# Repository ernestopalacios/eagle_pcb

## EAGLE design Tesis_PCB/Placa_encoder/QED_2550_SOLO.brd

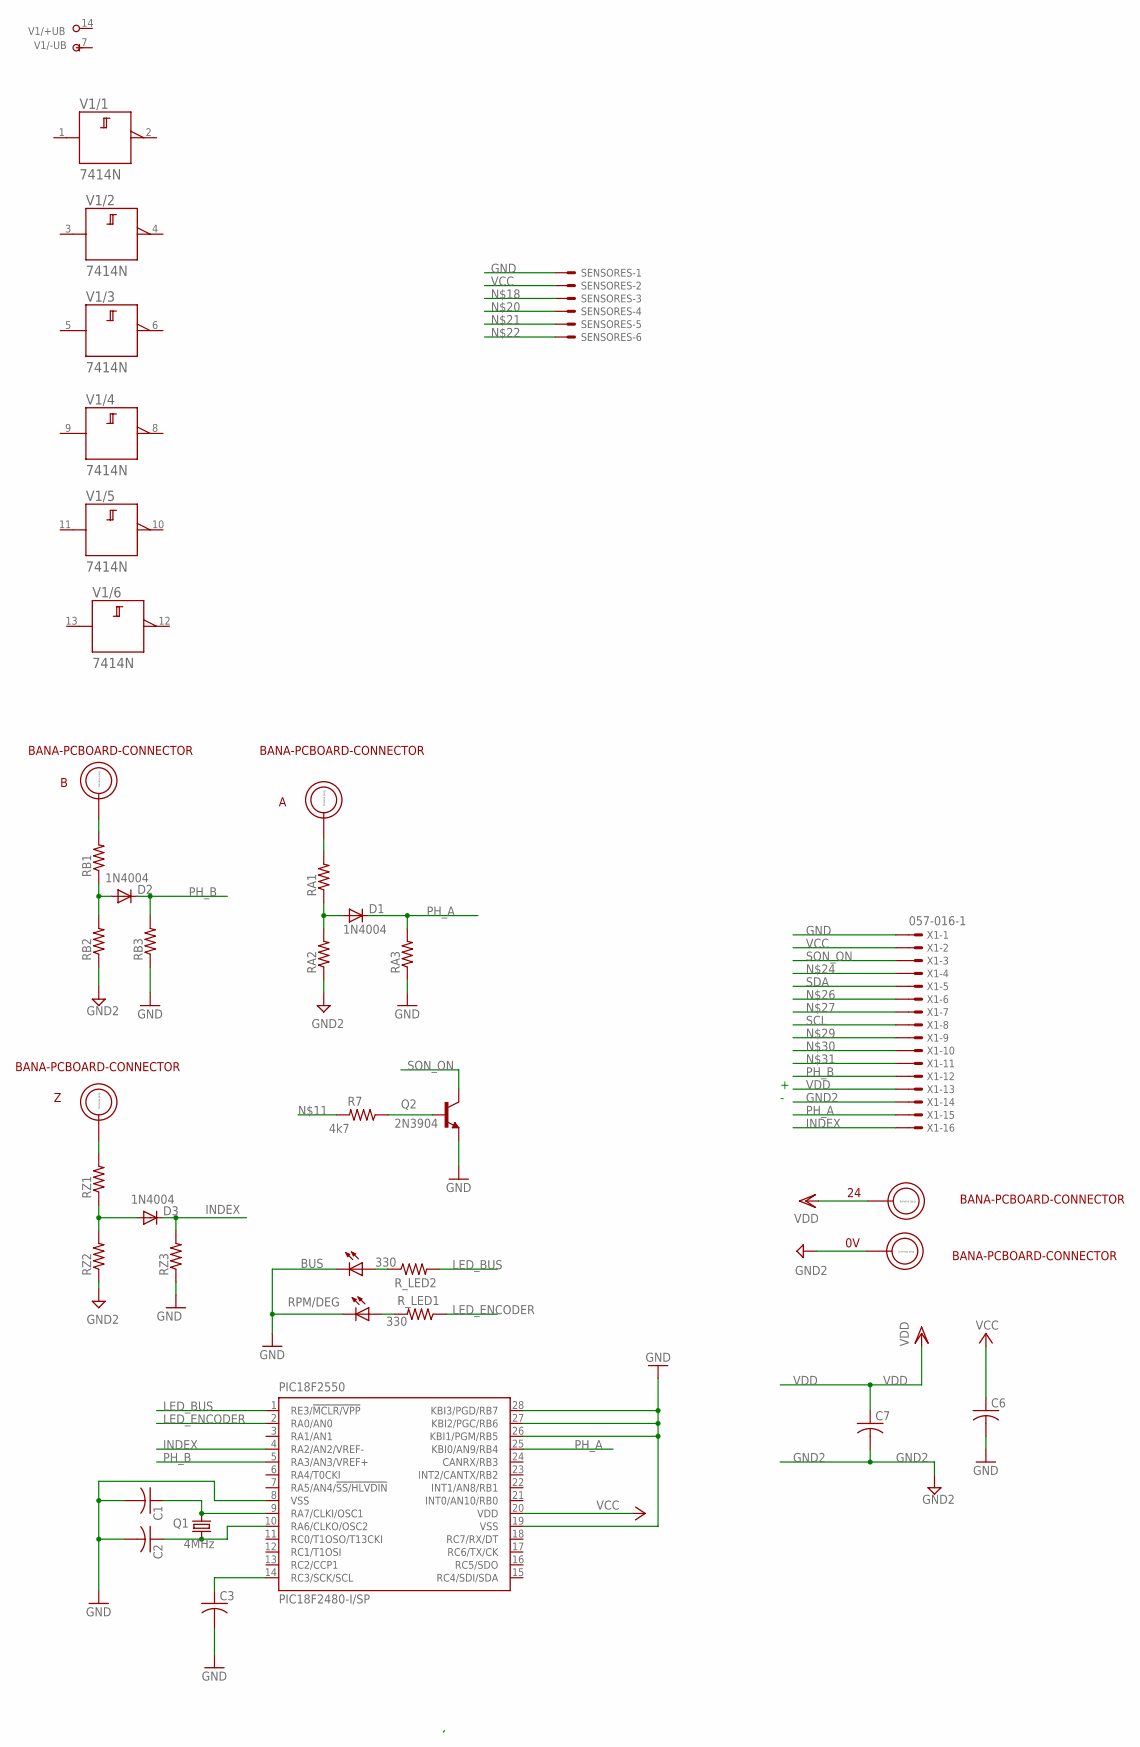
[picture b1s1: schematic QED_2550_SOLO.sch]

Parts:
0V, 24: BANA-PCBOARD-CONNECTOR; BANA_PLUG
A: BANA-PCBOARD-CONNECTOR; BANA_PLUG
B: BANA-PCBOARD-CONNECTOR; BANA_PLUG
BUS: LED5MM
C1, C2, C3: C-US025-024X044; C025-024X044
C6, C7: C-US025-030X050; C025-030X050
D1, D2, D3: 1N4004; DO41-10
PIC18F2550: PIC18F2480-I/SP; DIL28-3
Q1: 4MHz; HC49/S
Q2: 2N3904; TO92
R7: 4k7; 0204/7
RA1, RA2, RA3: R-US_0204/7; 0204/7
RB1, RB2, RB3: R-US_0204/7; 0204/7
RPM/DEG: LED5MM
RZ1, RZ2, RZ3: R-US_0204/7; 0204/7
R_LED1, R_LED2: 330; 0204/7
SENSORES: 22-23-2061
V1: 7414N; DIL14
X1: 057-016-1
Z: BANA-PCBOARD-CONNECTOR; BANA_PLUG

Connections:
+UB: V1.14 (+UB)
-UB: V1.7 (-UB)
GND: BUS.K (C), C1.2, C2.2, C3.2, C6.2, PIC18F2550.8 (VSS), PIC18F2550.19 (VSS), PIC18F2550.26 (KBI1/PGM/RB5), PIC18F2550.27 (KBI2/PGC/RB6), PIC18F2550.28 (KBI3/PGD/RB7), Q2.3 (E), RA3.1, RB3.1, RPM/DEG.K (C), RZ3.1, SENSORES.1, X1.1
GND2: 0V.P$1, C7.2, RA2.1, RB2.1, RZ2.1, X1.14
INDEX: D3.C, PIC18F2550.4 (RA2/AN2/VREF-), RZ3.2, X1.16
LED_BUS: PIC18F2550.1 (RE3/!MCLR/VPP), R_LED2.2
LED_ENCODER: PIC18F2550.2 (RA0/AN0), R_LED1.1
unnamed: C1.1, PIC18F2550.9 (RA7/CLKI/OSC1), Q1.2
unnamed: C2.1, PIC18F2550.10 (RA6/CLKO/OSC2), Q1.1
unnamed: C3.1, PIC18F2550.14 (RC3/SCK/SCL)
unnamed: BUS.A, R_LED2.1
unnamed: RPM/DEG.A, R_LED1.2
unnamed: D1.A, RA1.1, RA2.2
unnamed: Q2.2 (B), R7.1
unnamed: D2.A, RB1.1, RB2.2
unnamed: RZ1.2, Z.P$1
unnamed: B.P$1, RB1.2
unnamed: A.P$1, RA1.2
unnamed: D3.A, RZ1.1, RZ2.2
PH_A: D1.C, PIC18F2550.25 (KBI0/AN9/RB4), RA3.2, X1.15
PH_B: D2.C, PIC18F2550.5 (RA3/AN3/VREF+), RB3.2, X1.12
SCL: X1.8
SDA: X1.5
SON_ON: Q2.1 (C), X1.3
VCC: C6.1, PIC18F2550.20 (VDD), SENSORES.2, X1.2
VDD: 24.P$1, C7.1, X1.13

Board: 2 copper layers, 33 parts (0 on the bottom side), 22 nets, no tracks yet.

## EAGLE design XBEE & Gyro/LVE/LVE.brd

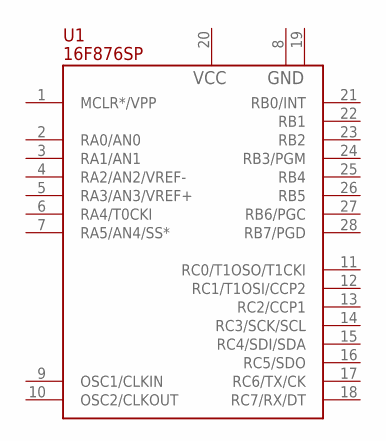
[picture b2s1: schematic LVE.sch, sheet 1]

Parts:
U1: 16F876SP; DIL28-3

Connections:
VCC: U1.20 (VCC); also elsewhere on the board

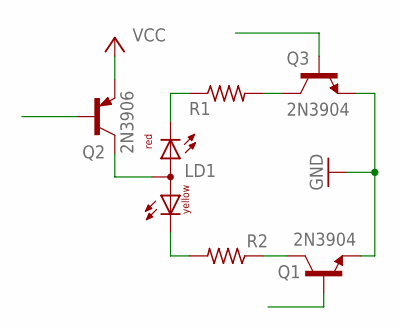
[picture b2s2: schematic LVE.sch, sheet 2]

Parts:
LD1: DUOLED-RY-A; DUOLED-A-5MM
Q1, Q3: 2N3904; TO92
Q2: 2N3906; TO92
R1, R2: R-US_0204/5; 0204/5

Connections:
GND: Q1.3 (E), Q3.3 (E)
unnamed: LD1.A, Q2.1 (C)
unnamed: LD1.CR, R1.1
unnamed: LD1.CX (CY), R2.2
unnamed: Q1.1 (C), R2.1
unnamed: Q3.1 (C), R1.2
VCC: Q2.3 (E); also elsewhere on the board

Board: 2 copper layers, 7 parts (0 on the bottom side), 7 nets, no tracks yet.

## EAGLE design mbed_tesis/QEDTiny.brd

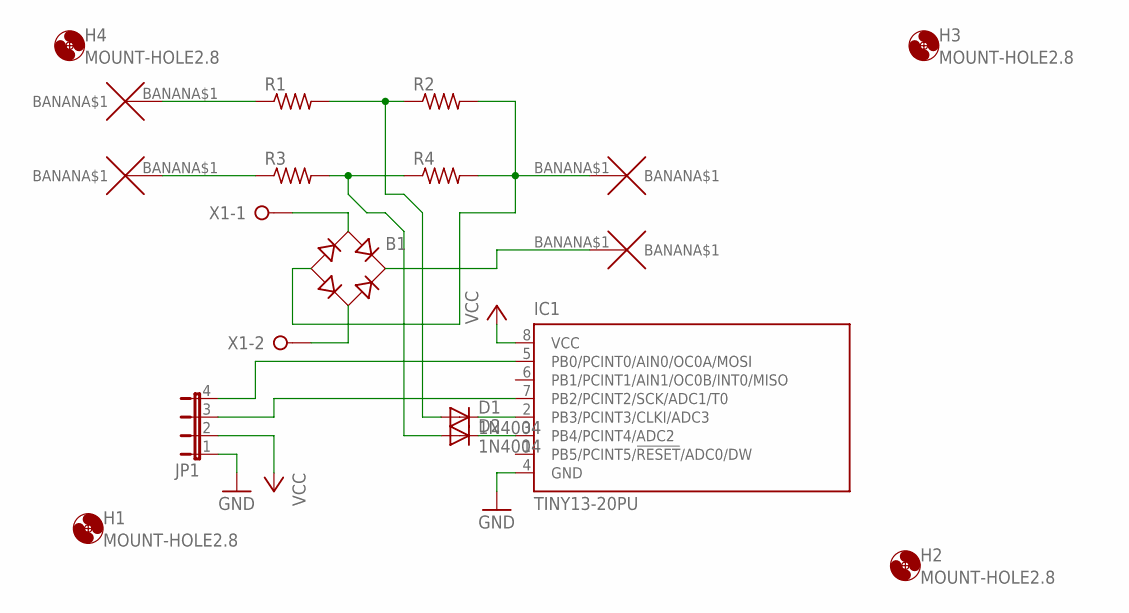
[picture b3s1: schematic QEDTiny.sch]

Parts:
B1: RB1A
D1, D2: 1N4004; DO41-10
H1, H2, H3, H4: MOUNT-HOLE2.8; 2,8
IC1: TINY13-20PU; DIL08
JP1: JP4E; JP4
R1, R2, R3, R4: R-US_0207/7; 0207/7
U$1, U$2, U$3, U$4: BANANA
X1: W237-02P; W237-132

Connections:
GND: IC1.4 (GND), JP1.1
unnamed: IC1.7 (PB2/PCINT2/SCK/ADC1/T0), JP1.3
unnamed: IC1.5 (PB0/PCINT0/AIN0/OC0A/MOSI), JP1.4
unnamed: R1.1, U$3.BANANA$1
unnamed: R3.1, U$4.BANANA$1
unnamed: D1.A, R1.2, R2.1
unnamed: D2.A, R3.2, R4.1
unnamed: B1.-, R2.2, R4.2, U$2.BANANA$1
unnamed: B1.AC1, X1.1
unnamed: B1.AC2, X1.2
unnamed: B1.+, U$1.BANANA$1
unnamed: D1.C, IC1.2 (PB3/PCINT3/CLKI/ADC3)
unnamed: D2.C, IC1.3 (PB4/PCINT4/ADC2)
VCC: IC1.8 (VCC), JP1.2

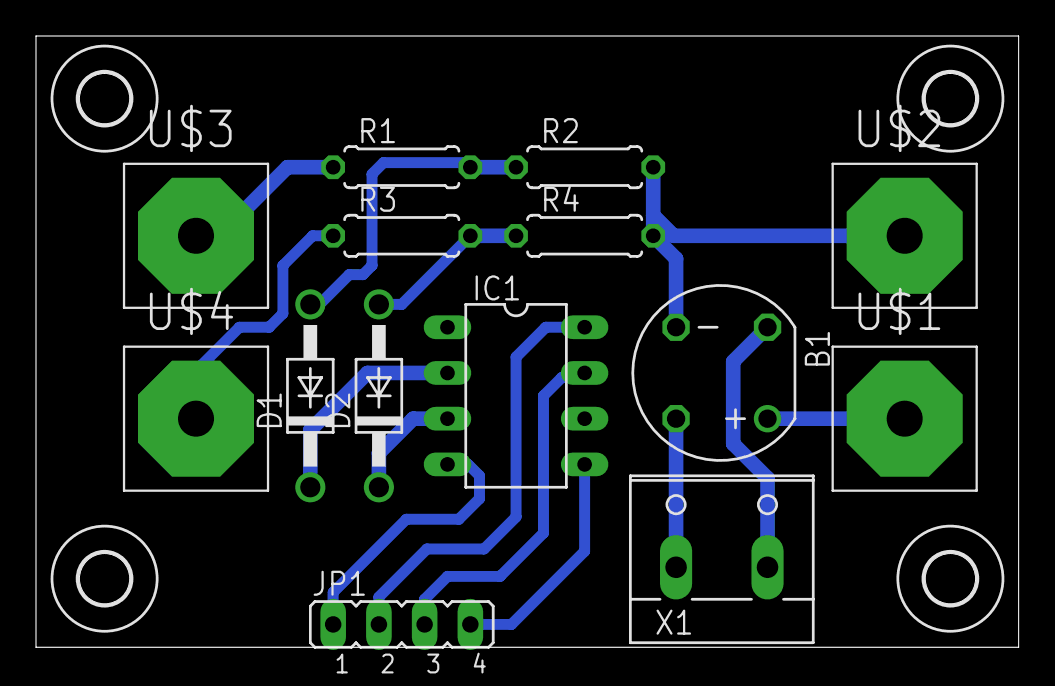
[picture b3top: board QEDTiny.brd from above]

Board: 2 copper layers, 54.6 x 34.0 mm, 18 parts (0 on the bottom side), 14 nets.
